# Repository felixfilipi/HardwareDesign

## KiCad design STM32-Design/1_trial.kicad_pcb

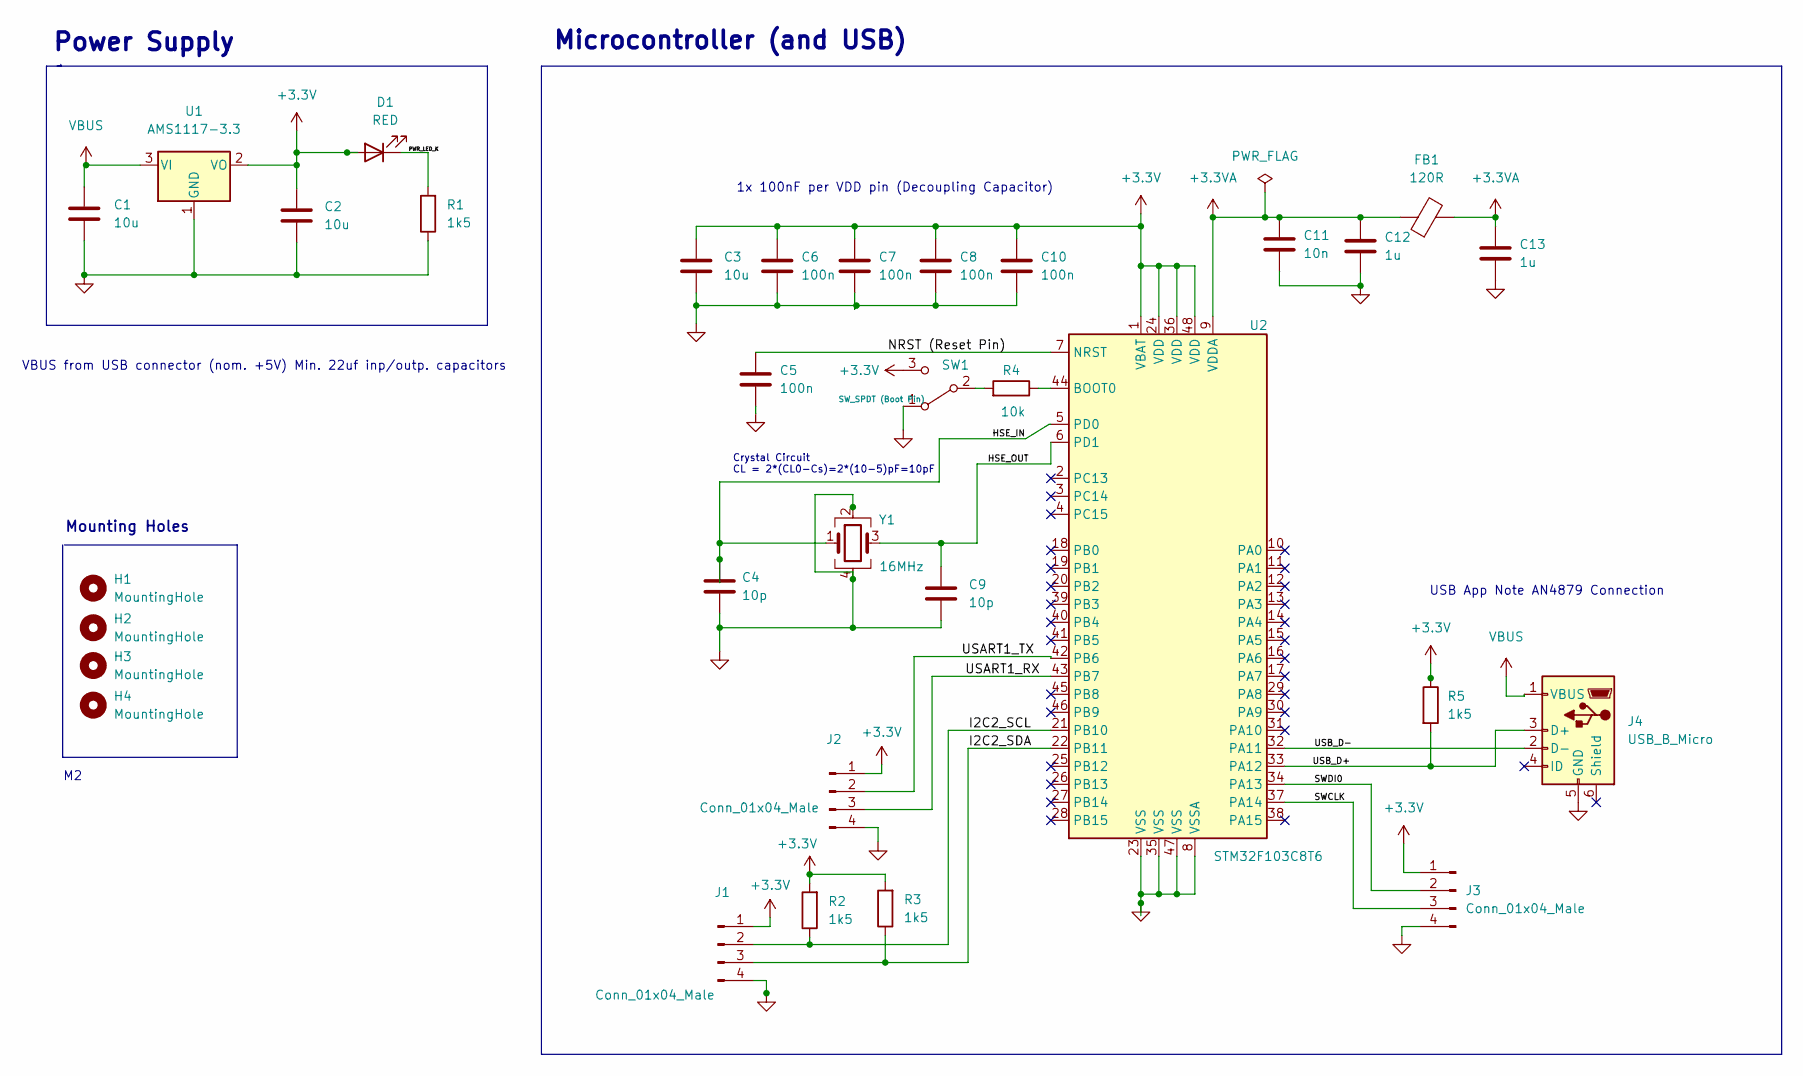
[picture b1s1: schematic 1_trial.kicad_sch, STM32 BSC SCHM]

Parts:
C1, C2, C3: 10u; C_0603_1608Metric
C4, C9: 10p; C_0402_1005Metric_Pad0.74x0.62mm_HandSolder
C5, C6, C7, C8, C10: 100n; C_0402_1005Metric_Pad0.74x0.62mm_HandSolder
C11: 10n; C_0402_1005Metric_Pad0.74x0.62mm_HandSolder
C12, C13: 1u; C_0402_1005Metric_Pad0.74x0.62mm_HandSolder
D1: RED; LED_0603_1608Metric
FB1: 120R; L_0603_1608Metric
H1, H2, H3, H4: MountingHole; MountingHole_2.2mm_M2
J1, J2, J3: Conn_01x04_Male; PinHeader_1x04_P2.00mm_Vertical
J4: USB_B_Micro; USB_Micro-B_Wuerth_629105150521
R1, R2, R3, R5: 1k5; R_0402_1005Metric
R4: 10k; R_0402_1005Metric
SW1: SW_SPDT (Boot Pin); SW_SPDT_PCM12
U1: AMS1117-3.3; SOT-223-3_TabPin2
U2: STM32F103C8T6; LQFP-48_7x7mm_P0.5mm
Y1: 16MHz; Crystal_SMD_3225-4Pin_3.2x2.5mm

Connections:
+3.3V: C2.1, C3.1, C6.1, C7.1, C8.1, C10.1, D1.2 (A), J1.1, J2.1, J3.1, R2.2, R3.2, R5.1, SW1.3 (C), U1.2 (VO), U2.1 (VBAT), U2.24 (VDD), U2.36 (VDD), U2.48 (VDD)
+3.3VA: C11.1, C12.1, C13.1, FB1.1, FB1.2, U2.9 (VDDA)
/HSE_IN: C4.1, U2.5 (PD0), Y1.1
/HSE_OUT: C9.1, U2.6 (PD1), Y1.3
/I2C2_SCL: J1.2, R2.1, U2.21 (PB10)
/I2C2_SDA: J1.3, R3.1, U2.22 (PB11)
/NRST (Reset Pin): C5.1, U2.7 (NRST)
/PWR_LED_K: D1.1 (K), R1.2
/SWCLK: J3.3, U2.37 (PA14)
/SWDI0: J3.2, U2.34 (PA13)
/USART1_RX: J2.3, U2.43 (PB7)
/USART1_TX: J2.2, U2.42 (PB6)
/USB_D+: J4.3 (D+), R5.2, U2.33 (PA12)
/USB_D-: J4.2 (D-), U2.32 (PA11)
GND: C1.2, C2.2, C3.2, C4.2, C5.2, C6.2, C7.2, C8.2, C9.2, C10.2, C11.2, C12.2, C13.2, J1.4, J2.4, J3.4, J4.5 (GND), R1.1, SW1.1 (A), U1.1 (GND), U2.8 (VSSA), U2.23 (VSS), U2.35 (VSS), U2.47 (VSS), Y1.2, Y1.4
unnamed: R4.1, U2.44 (BOOT0)
unnamed: R4.2, SW1.2 (B)
VBUS: C1.1, J4.1 (VBUS), U1.3 (VI)

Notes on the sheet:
Power Supply
Microcontroller (and USB)
1x 100nF per VDD pin (Decoupling Capacitor)
VBUS from USB connector (nom. +5V) Min. 22uf inp/outp. capacitors
USB App Note AN4879 Connection
Crystal Circuit CL = 2*(CL0-Cs)=2*(10-5)pF=10pF
Mounting Holes

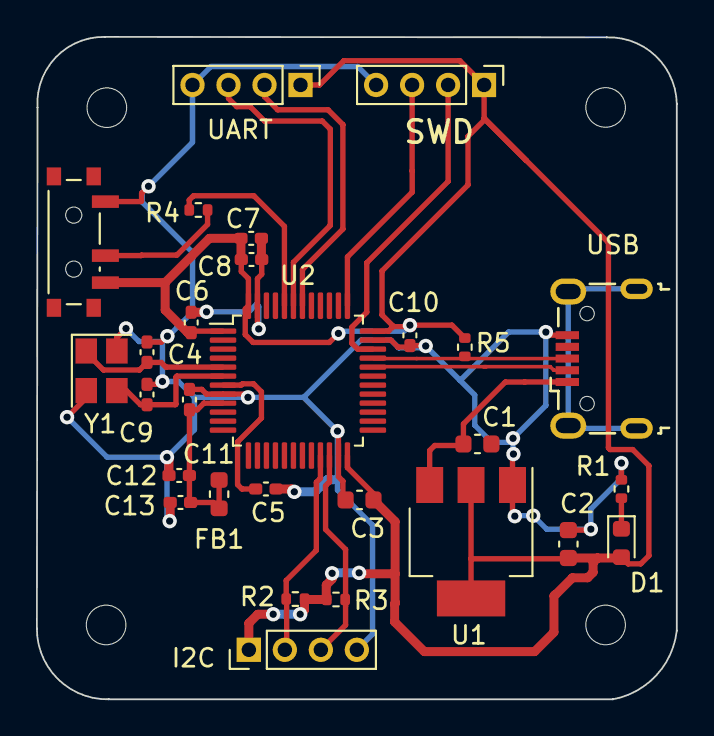
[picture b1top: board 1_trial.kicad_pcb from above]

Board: 2 copper layers, 35.5 x 36.8 mm, 32 parts (0 on the bottom side), 18 nets.

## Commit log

2022-11-04 STM32-Design
2022-11-04 Change proj name
2022-11-04 Documentation
